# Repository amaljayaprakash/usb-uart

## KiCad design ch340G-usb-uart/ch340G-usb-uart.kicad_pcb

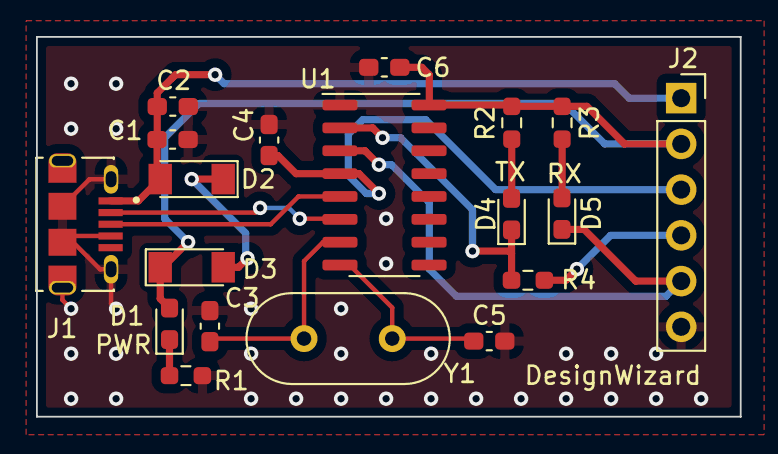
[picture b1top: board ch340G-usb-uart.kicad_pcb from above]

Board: 2 copper layers, 39.1 x 21.1 mm, 19 parts (0 on the bottom side), 15 nets.

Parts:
C1: 10uF; C_0603_1608Metric_Pad1.08x0.95mm_HandSolder
C2, C4, C6: 100n; C_0603_1608Metric_Pad1.08x0.95mm_HandSolder
C3, C5: 22p; C_0603_1608Metric_Pad1.08x0.95mm_HandSolder
D1: RED; LED_0603_1608Metric_Pad1.05x0.95mm_HandSolder
D2, D3: LL4148; D_MiniMELF
D4: AMBR; LED_0603_1608Metric_Pad1.05x0.95mm_HandSolder
D5: GREN; LED_0603_1608Metric_Pad1.05x0.95mm_HandSolder
J1: 10118194-0001LF; AMPHENOL_10118194-0001LF
J2: TTL OUT; PinSocket_1x06_P2.54mm_Vertical
R1, R2, R3, R4: 1.5k; R_0603_1608Metric_Pad0.98x0.95mm_HandSolder
U1: CH340G; SOIC-16_3.9x9.9mm_P1.27mm
Y1: 12MHz; Crystal_HC18-U_Vertical

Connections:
+3V3: C4.1, J2.3, U1.4 (V3)
+5V: C1.1, C2.1, D2.2 (A), J1.1, J2.1
GND: C1.2, C2.2, C3.2, C4.2, C5.2, C6.2, J1.4, J1.S1 (SHIELD), J1.S2 (SHIELD), J1.S3 (SHIELD), J1.S4 (SHIELD), J1.S5 (SHIELD), J1.S6 (SHIELD), J2.6, R1.2, U1.1 (GND)
unnamed: C3.1, U1.7 (XI), Y1.1
unnamed: C5.1, U1.8 (XO), Y1.2
unnamed: C6.1, D1.2 (A), D3.1 (K), J2.2, R2.1, R3.1, U1.16 (VCC)
unnamed: D1.1 (K), R1.1
unnamed: D2.1 (K), D3.2 (A)
unnamed: D4.1 (K), R4.1, U1.2 (TXD)
unnamed: D4.2 (A), R2.2
unnamed: D5.1 (K), J2.5, U1.3 (RXD)
unnamed: D5.2 (A), R3.2
unnamed: J1.2, U1.6 (UD-)
unnamed: J1.3, U1.5 (UD+)
unnamed: J2.4, R4.2

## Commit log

2023-06-14 added J2 Legends
